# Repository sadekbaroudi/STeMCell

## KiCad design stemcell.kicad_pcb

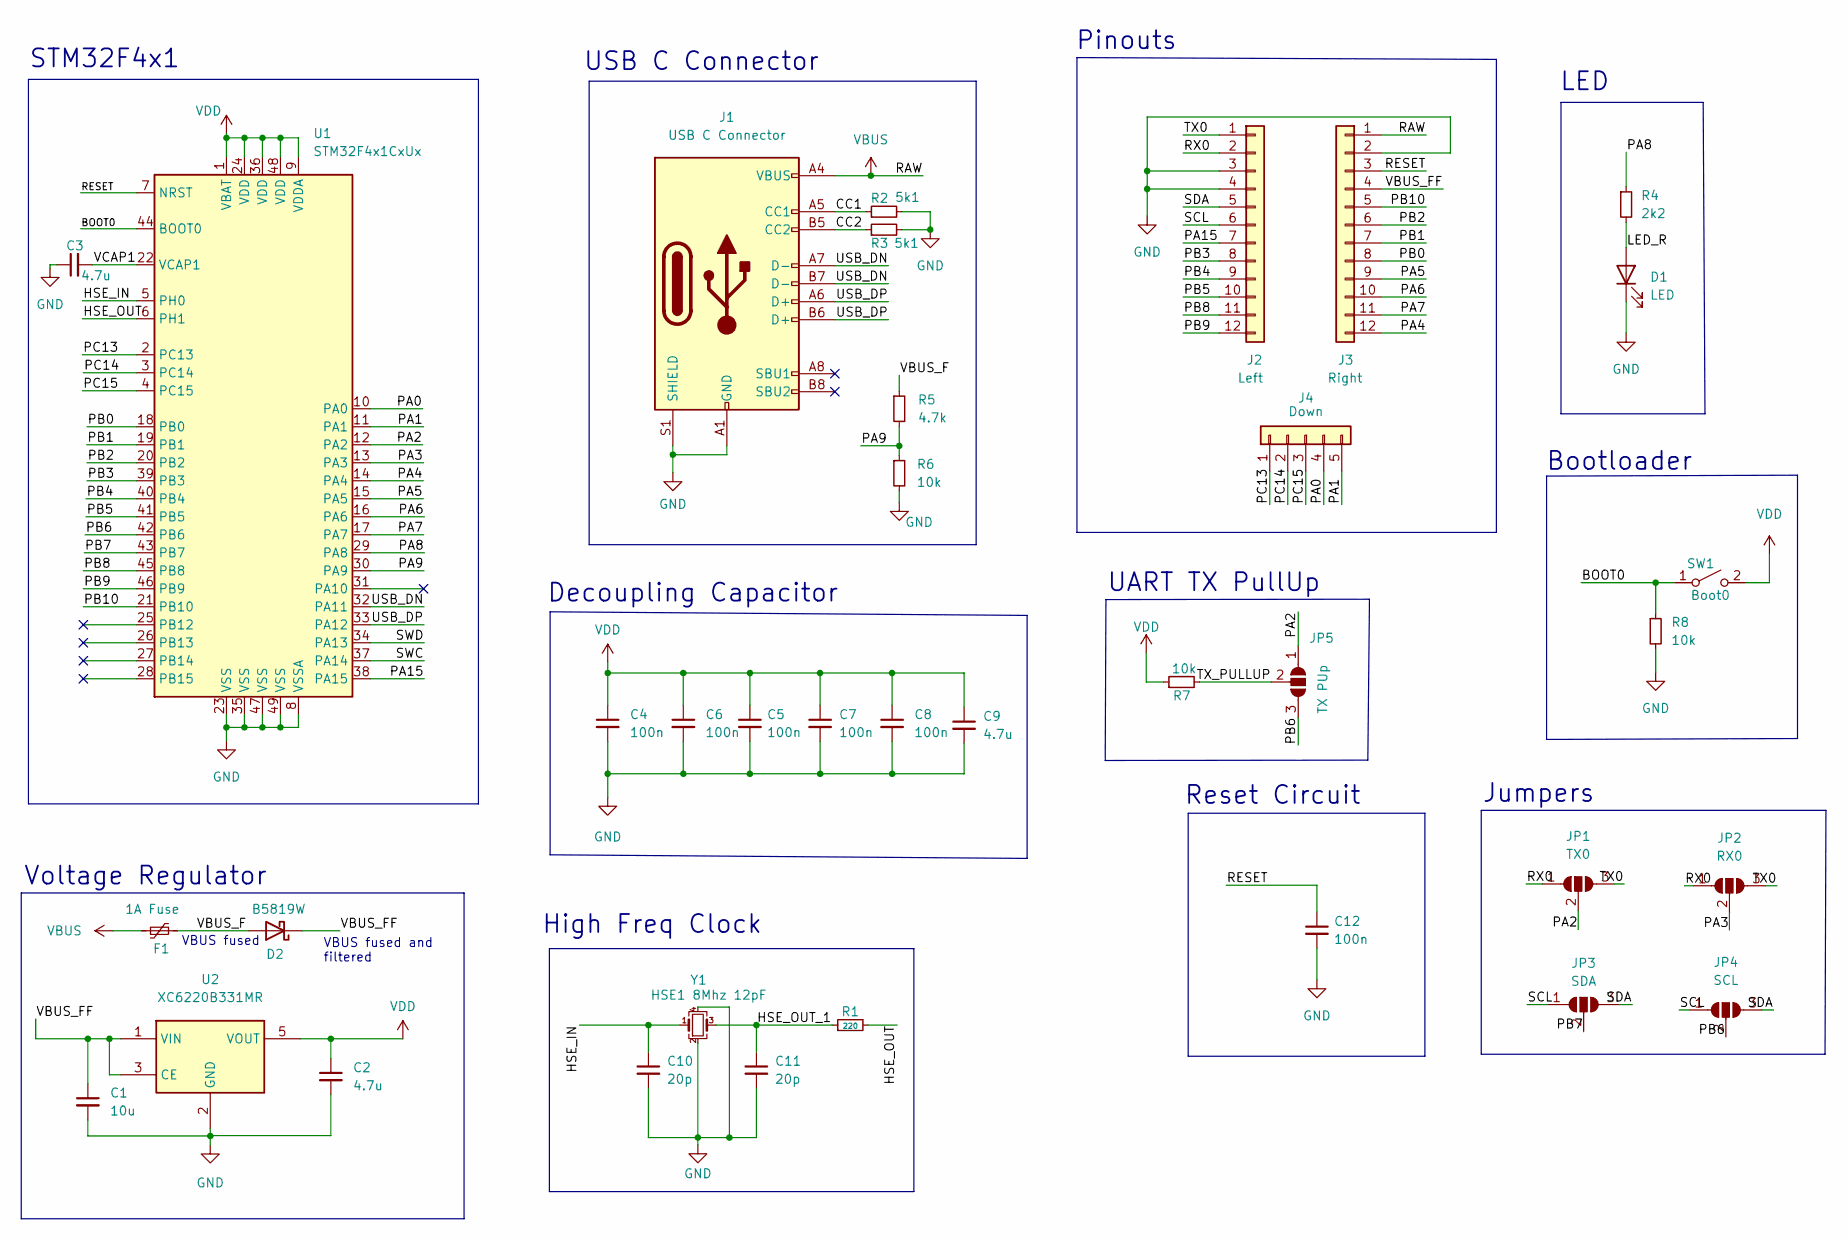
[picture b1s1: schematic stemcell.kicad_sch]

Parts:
C1: 10u; C_0402_1005Metric; LCSC C15525
C2, C3, C9: 4.7u; C_0402_1005Metric; LCSC C23733
C4, C5, C6, C7, C8, C12: 100n; C_0402_1005Metric; LCSC C1525
C10, C11: 20p; C_0402_1005Metric; LCSC C1554
D1: LED; LED_0402_1005Metric; LCSC C130724
D2: B5819W; D_SOD-123; LCSC C8598
F1: 1A Fuse; Fuse_0805_2012Metric; LCSC C135329
J1: USB C Connector; USB_C_Receptacle_HRO_TYPE-C-31-M-12; LCSC C165948
J2: Left; Pins12_castellated
J3: Right; Pins12_castellated
J4: Down; Pins5_castellated
JP1: TX0; SOLDER_JUMPER_3_2_3
JP2: RX0; SOLDER_JUMPER_3_1_2
JP3: SDA; SOLDER_JUMPER_3_2_3
JP4: SCL; SOLDER_JUMPER_3_1_2
JP5: TX PUp; SOLDER_JUMPER_3
R1: 220; R_0402_1005Metric; LCSC C25091
R2, R3: 5k1; R_0402_1005Metric; LCSC C25905
R4: 2k2; R_0402_1005Metric; LCSC C25879
R5: 4.7k; R_0402_1005Metric; LCSC C25900
R6, R7, R8: 10k; R_0402_1005Metric; LCSC C25744
SW1: Boot0; SW_SPST_CK_KXT3; LCSC C319433
U1: STM32F4x1CxUx; QFN-48-1EP_7x7mm_P0.5mm_EP5.6x5.6mm; LCSC C60420
U2: XC6220B331MR; SOT-23-5; LCSC C86534
Y1: HSE1 8Mhz 12pF; Crystal_SMD_3225-4Pin_3.2x2.5mm; LCSC C2682775

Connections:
/BOOT0: R8.1, SW1.1 (A), U1.44 (BOOT0)
/CC1: J1.A5 (CC1), R2.1
/CC2: J1.B5 (CC2), R3.1
/HSE_IN: C10.1, U1.5 (PH0), Y1.1
/HSE_OUT: R1.2, U1.6 (PH1)
/HSE_OUT_1: C11.1, R1.1, Y1.3
/LED_R: D1.2 (A), R4.2
/PA0: J4.4, U1.10 (PA0)
/PA1: J4.5, U1.11 (PA1)
/PA2: JP1.2 (C), JP5.1 (A), U1.12 (PA2)
/PA3: JP2.2 (C), U1.13 (PA3)
/PA4: J3.12, U1.14 (PA4)
/PA5: J3.9, U1.15 (PA5)
/PA6: J3.10, U1.16 (PA6)
/PA7: J3.11, U1.17 (PA7)
/PA8: R4.1, U1.29 (PA8)
/PA9: R5.2, R6.1, U1.30 (PA9)
/PA15: J2.7, U1.38 (PA15)
/PB0: J3.8, U1.18 (PB0)
/PB1: J3.7, U1.19 (PB1)
/PB2: J3.6, U1.20 (PB2)
/PB3: J2.8, U1.39 (PB3)
/PB4: J2.9, U1.40 (PB4)
/PB5: J2.10, U1.41 (PB5)
/PB6: JP4.2 (C), JP5.3 (B), U1.42 (PB6)
/PB7: JP3.2 (C), U1.43 (PB7)
/PB8: J2.11, U1.45 (PB8)
/PB9: J2.12, U1.46 (PB9)
/PB10: J3.5, U1.21 (PB10)
/PC13: J4.1, U1.2 (PC13)
/PC14: J4.2, U1.3 (PC14)
/PC15: J4.3, U1.4 (PC15)
/RESET: C12.1, J3.3, U1.7 (NRST)
/RX0: J2.2, JP1.1 (A), JP2.1 (A)
/SCL: J2.6, JP3.1 (A), JP4.1 (A)
/SDA: J2.5, JP3.3 (B), JP4.3 (B)
/SWC: U1.37 (PA14)
/SWD: U1.34 (PA13)
/TX0: J2.1, JP1.3 (B), JP2.3 (B)
/TX_PULLUP: JP5.2 (C), R7.2
/USB_DN: J1.A7 (D-), J1.B7 (D-), U1.32 (PA11)
/USB_DP: J1.A6 (D+), J1.B6 (D+), U1.33 (PA12)
/VBUS_F: D2.2 (A), F1.2, R5.1
/VBUS_FF: C1.1, D2.1 (K), J3.4, U2.1 (VIN), U2.3 (CE)
/VCAP1: C3.2, U1.22 (VCAP1)
GND: C1.2, C2.2, C3.1, C4.2, C5.2, C6.2, C7.2, C8.2, C9.2, C10.2, C11.2, C12.2, D1.1 (K), J1.A1 (GND), J1.A12 (GND), J1.B1 (GND), J1.B12 (GND), J1.S1 (SHIELD), J2.3, J2.4, J3.2, R2.2, R3.2, R6.2, R8.2, U1.8 (VSSA), U1.23 (VSS), U1.35 (VSS), U1.47 (VSS), U1.49 (VSS), U2.2 (GND), Y1.2, Y1.4
VBUS: F1.1, J1.A4 (VBUS), J1.A9 (VBUS), J1.B4 (VBUS), J1.B9 (VBUS), J3.1
VDD: C2.1, C4.1, C5.1, C6.1, C7.1, C8.1, C9.1, R7.1, SW1.2 (B), U1.1 (VBAT), U1.9 (VDDA), U1.24 (VDD), U1.36 (VDD), U1.48 (VDD), U2.5 (VOUT)

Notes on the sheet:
Jumpers
Decoupling Capacitor
STM32F4x1
Reset Circuit
VBUS fused
Voltage Regulator
LED
High Freq Clock
Bootloader
UART TX PullUp
USB C Connector
VBUS fused and filtered
Pinouts

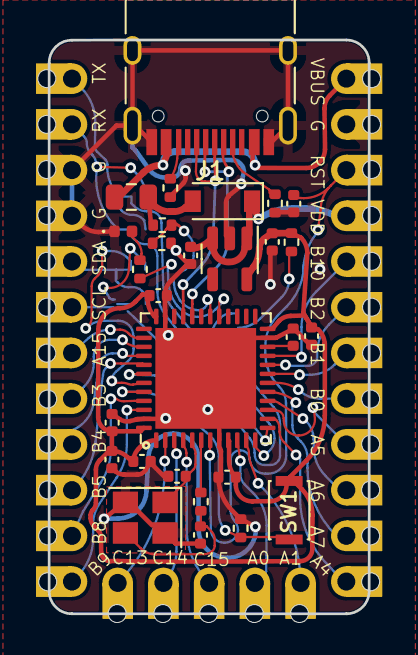
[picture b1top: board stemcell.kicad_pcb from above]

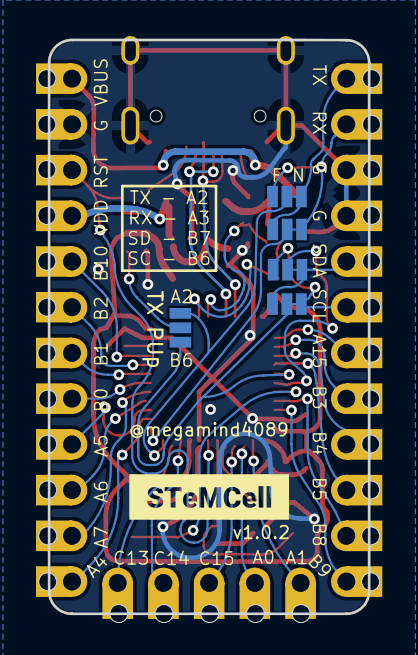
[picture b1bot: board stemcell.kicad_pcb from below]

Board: 2 copper layers, 17.8 x 31.9 mm, 37 parts (7 on the bottom side), 46 nets.

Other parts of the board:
kibuzzard-620B7294: G***; kibuzzard-620B7294

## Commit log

2022-02-15 Update docs
2022-03-09 Add pinout page
2022-04-27 updated to use type-c-31-m-12, since it's more commonly available
2022-10-14 added pre-soldered jumpers on the N position, can be cut with razor blade to remove
